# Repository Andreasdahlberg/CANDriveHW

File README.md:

# CANDriveHW
CANDrive is a brushed DC Motor Controller controlled via a CAN interface.

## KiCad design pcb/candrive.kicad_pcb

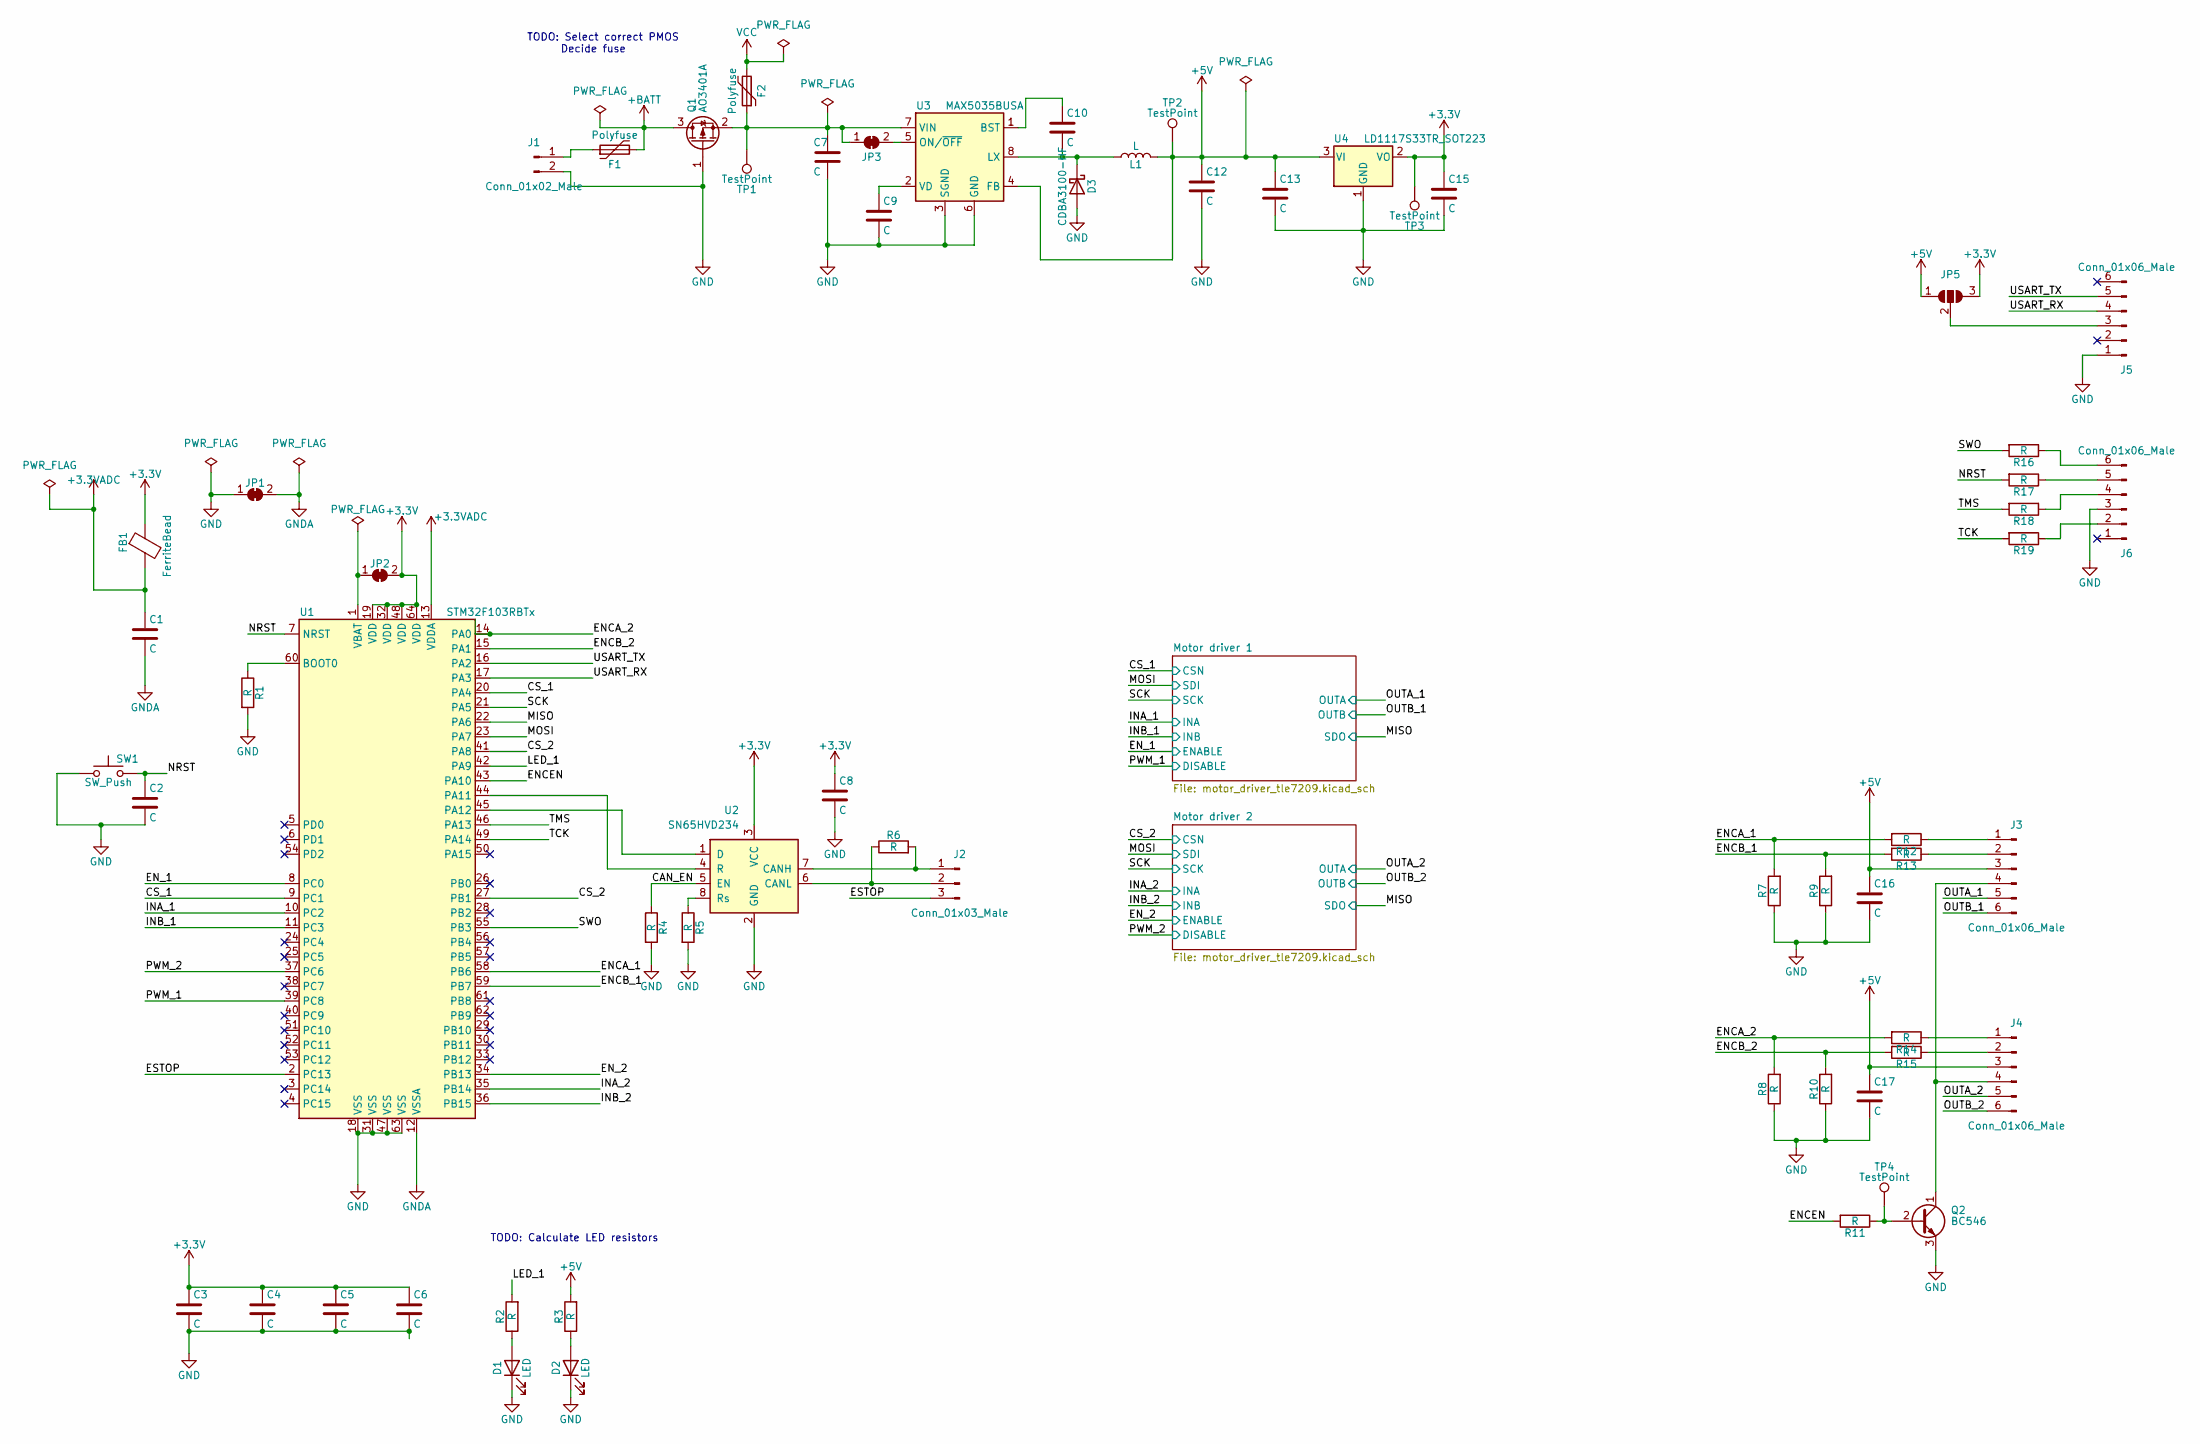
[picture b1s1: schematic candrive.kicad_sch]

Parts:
C1, C2, C3, C4, C5, C6, C7, C8, C9, C10, C12, C13, C15, C16, C17: C; C_0805_2012Metric_Pad1.18x1.45mm_HandSolder
D1, D2: LED; LED_0805_2012Metric_Pad1.15x1.40mm_HandSolder
D3: CDBA3100-HF; D_SMA
F1, F2: Polyfuse; Fuse_Bourns_MF-RHT300
FB1: FerriteBead; LairdTech_28C0236-0JW-10
J1: Conn_01x02_Male; PinHeader_1x02_P2.54mm_Horizontal
J2: Conn_01x03_Male; PinHeader_1x03_P2.54mm_Horizontal
J3, J4: Conn_01x06_Male; PinHeader_1x06_P2.54mm_Horizontal
J5, J6: Conn_01x06_Male; PinHeader_1x06_P2.54mm_Vertical
JP1, JP2, JP3: SolderJumper_2_Bridged; SolderJumper-2_P1.3mm_Open_TrianglePad1.0x1.5mm
JP5: SolderJumper_3_Open; SolderJumper-3_P2.0mm_Open_TrianglePad1.0x1.5mm
L1: L; L_0805_2012Metric_Pad1.05x1.20mm_HandSolder
Q1: AO3401A; SOT-23
Q2: BC546; TO-92_Inline
R1, R2, R3, R4, R5, R6, R7, R8, R9, R10, R11, R12, R13, R14, R15, R16, R17, R18, R19: R; R_0805_2012Metric_Pad1.20x1.40mm_HandSolder
SW1: SW_Push; SW_Push_1P1T_NO_CK_KSC6xxJ
TP1, TP2, TP3, TP4: TestPoint; TestPoint_THTPad_D1.0mm_Drill0.5mm
U1: STM32F103RBTx; LQFP-64_10x10mm_P0.5mm
U2: SN65HVD234; SOIC-8_3.9x4.9mm_P1.27mm
U3: MAX5035BUSA; SOIC-8_3.9x4.9mm_P1.27mm
U4: LD1117S33TR_SOT223; SOT-223-3_TabPin2

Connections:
+3.3V: C3.1, C4.1, C5.1, C6.1, C8.1, C15.1, FB1.1, JP2.2 (B), JP5.3 (B), TP3.1, U1.19 (VDD), U1.32 (VDD), U1.48 (VDD), U1.64 (VDD), U2.3 (VCC), U4.2 (VO)
+3.3VADC: C1.1, FB1.2, U1.13 (VDDA)
+5V: C12.1, C13.1, C16.1, C17.1, J3.3, J4.3, JP5.1 (A), L1.2, R3.2, TP2.1, U3.4 (FB), U4.3 (VI)
+BATT: F1.2, Q1.3 (D)
/CAN_EN: R4.1, U2.5 (EN)
/CS_1: U1.9 (PC1), U1.20 (PA4); also elsewhere on the board
/CS_2: U1.27 (PB1), U1.41 (PA8); also elsewhere on the board
/ENCA_1: R7.2, R12.2, U1.58 (PB6)
/ENCA_2: R8.2, R14.2, U1.14 (PA0)
/ENCB_1: R9.2, R13.2, U1.59 (PB7)
/ENCB_2: R10.2, R15.2, U1.15 (PA1)
/ENCEN: R11.2, U1.43 (PA10)
/EN_1: U1.8 (PC0); also elsewhere on the board
/EN_2: U1.34 (PB13); also elsewhere on the board
/ESTOP: J2.3, U1.2 (PC13)
/INA_1: U1.10 (PC2); also elsewhere on the board
/INA_2: U1.35 (PB14); also elsewhere on the board
/INB_1: U1.11 (PC3); also elsewhere on the board
/INB_2: U1.36 (PB15); also elsewhere on the board
/LED_1: R2.2, U1.42 (PA9)
/MISO: U1.22 (PA6); also elsewhere on the board
/MOSI: U1.23 (PA7); also elsewhere on the board
/NRST: C2.1, R17.2, SW1.2, U1.7 (NRST)
/OUTA_1: J3.5; also elsewhere on the board
/OUTA_2: J4.5; also elsewhere on the board
/OUTB_1: J3.6; also elsewhere on the board
/OUTB_2: J4.6; also elsewhere on the board
/PWM_1: U1.39 (PC8); also elsewhere on the board
/PWM_2: U1.37 (PC6); also elsewhere on the board
/SCK: U1.21 (PA5); also elsewhere on the board
/SWO: R16.2, U1.55 (PB3)
/TCK: R19.2, U1.49 (PA14)
/TMS: R18.2, U1.46 (PA13)
/USART_RX: J5.4, U1.17 (PA3)
/USART_TX: J5.5, U1.16 (PA2)
GND: C2.2, C3.2, C4.2, C5.2, C6.2, C7.2, C8.2, C9.2, C12.2, C13.2, C15.2, C16.2, C17.2, D1.1 (K), D2.1 (K), D3.2 (A), J1.2, J5.1, J6.3, JP1.1 (A), Q1.1 (G), Q2.3 (E), R1.2, R4.2, R5.2, R7.1, R8.1, R9.1, R10.1, SW1.1, U1.18 (VSS), U1.31 (VSS), U1.47 (VSS), U1.63 (VSS), U2.2 (GND), U3.3 (SGND), U3.6 (GND), U4.1 (GND); also elsewhere on the board
GNDA: C1.2, JP1.2 (B), U1.12 (VSSA)
unnamed: C7.1, F2.1, JP3.1 (A), Q1.2 (S), TP1.1, U3.7 (VIN)
unnamed: C9.1, U3.2 (VD)
unnamed: C10.1, U3.1 (BST)
unnamed: C10.2, D3.1 (K), L1.1, U3.8 (LX)
unnamed: D1.2 (A), R2.1
unnamed: D2.2 (A), R3.1
unnamed: F1.1, J1.1
unnamed: J2.1, R6.2, U2.7 (CANH)
unnamed: J2.2, R6.1, U2.6 (CANL)
unnamed: J3.1, R12.1
unnamed: J3.2, R13.1
unnamed: J3.4, J4.4, Q2.1 (C)
unnamed: J4.1, R14.1
unnamed: J4.2, R15.1
unnamed: J5.3, JP5.2 (C)
unnamed: J6.2, R19.1
unnamed: J6.4, R18.1
unnamed: J6.5, R17.1
unnamed: J6.6, R16.1
unnamed: JP2.1 (A), U1.1 (VBAT)
unnamed: JP3.2 (B), U3.5 (ON/~OFF)
unnamed: Q2.2 (B), R11.1, TP4.1
unnamed: R1.1, U1.60 (BOOT0)
unnamed: R5.1, U2.8 (Rs)
unnamed: U1.44 (PA11), U2.4 (R)
unnamed: U1.45 (PA12), U2.1 (D)
VCC: F2.2; also elsewhere on the board

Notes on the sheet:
TODO: Calculate LED resistors
TODO: Select correct PMOS Decide fuse

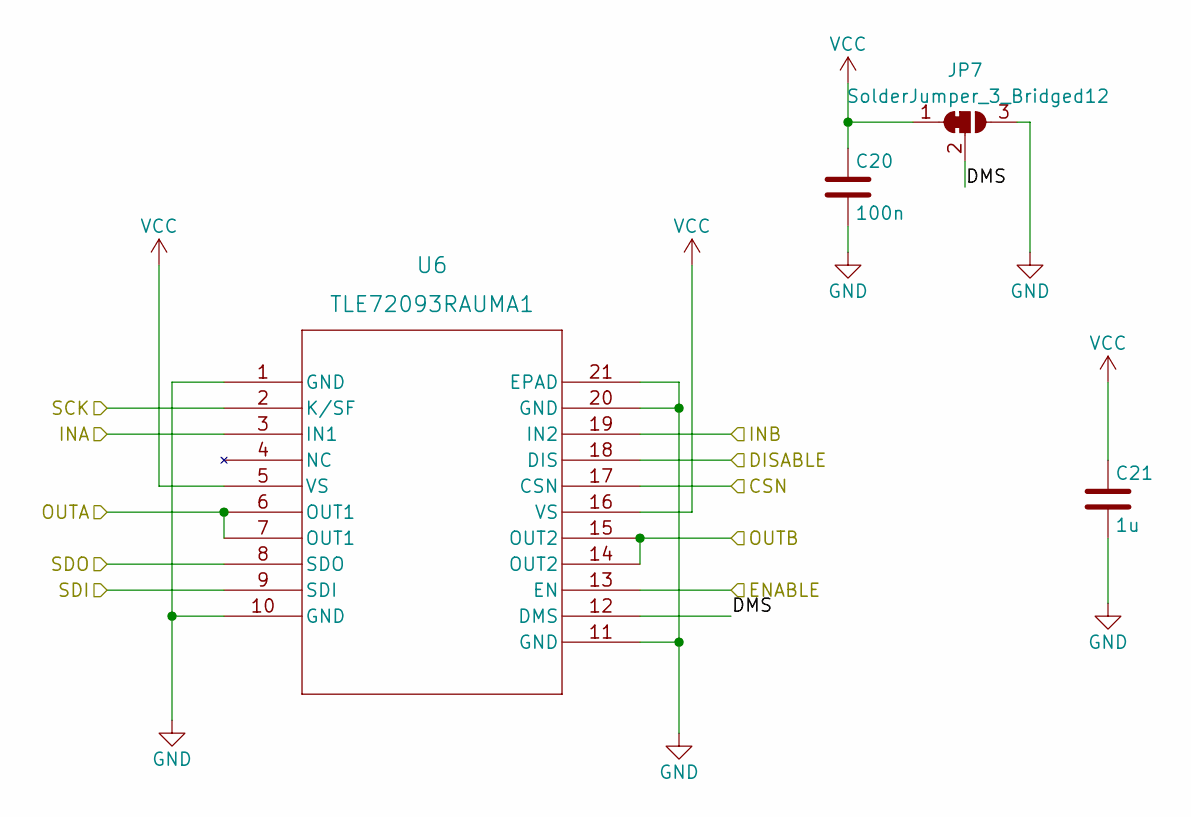
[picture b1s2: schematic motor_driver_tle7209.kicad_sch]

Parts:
C20: 100n; C_0805_2012Metric_Pad1.18x1.45mm_HandSolder
C21: 1u; C_0805_2012Metric_Pad1.18x1.45mm_HandSolder
JP7: SolderJumper_3_Bridged12; SolderJumper-3_P2.0mm_Open_TrianglePad1.0x1.5mm
U6: TLE72093RAUMA1; PG-DSO-20-65_11X15P9_INF

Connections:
/CS_1: U6.17 (CSN); also elsewhere on the board
/EN_1: U6.13 (EN); also elsewhere on the board
/INA_1: U6.3 (IN1); also elsewhere on the board
/INB_1: U6.19 (IN2); also elsewhere on the board
/MISO: U6.8 (SDO); also elsewhere on the board
/MOSI: U6.9 (SDI); also elsewhere on the board
/Motor driver 1/DMS: JP7.2 (C), U6.12 (DMS)
/OUTA_1: U6.6 (OUT1), U6.7 (OUT1); also elsewhere on the board
/OUTB_1: U6.14 (OUT2), U6.15 (OUT2); also elsewhere on the board
/PWM_1: U6.18 (DIS); also elsewhere on the board
/SCK: U6.2 (K/SF); also elsewhere on the board
GND: C20.2, C21.2, JP7.3 (B), U6.1 (GND), U6.10 (GND), U6.11 (GND), U6.20 (GND), U6.21 (EPAD); also elsewhere on the board
VCC: C20.1, C21.1, JP7.1 (A), U6.5 (VS), U6.16 (VS); also elsewhere on the board

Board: 4 copper layers, 70 parts (0 on the bottom side), 66 nets, no tracks yet.

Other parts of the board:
C18: 100n; C_0805_2012Metric_Pad1.18x1.45mm_HandSolder
C19: 1u; C_0805_2012Metric_Pad1.18x1.45mm_HandSolder
JP6: SolderJumper_3_Bridged12; SolderJumper-3_P2.0mm_Open_TrianglePad1.0x1.5mm
U5: TLE72093RAUMA1; PG-DSO-20-65_11X15P9_INF

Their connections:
/CS_2: U5.17 (CSN); also elsewhere on the board
/EN_2: U5.13 (EN); also elsewhere on the board
/INA_2: U5.3 (IN1); also elsewhere on the board
/INB_2: U5.19 (IN2); also elsewhere on the board
/MISO: U5.8 (SDO); also elsewhere on the board
/MOSI: U5.9 (SDI); also elsewhere on the board
/Motor driver 2/DMS: JP6.2 (C), U5.12 (DMS)
/OUTA_2: U5.6 (OUT1), U5.7 (OUT1); also elsewhere on the board
/OUTB_2: U5.14 (OUT2), U5.15 (OUT2); also elsewhere on the board
/PWM_2: U5.18 (DIS); also elsewhere on the board
/SCK: U5.2 (K/SF); also elsewhere on the board
GND: C18.2, C19.2, JP6.3 (B), U5.1 (GND), U5.10 (GND), U5.11 (GND), U5.20 (GND), U5.21 (EPAD); also elsewhere on the board
VCC: C18.1, C19.1, JP6.1 (A), U5.5 (VS), U5.16 (VS); also elsewhere on the board

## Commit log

2023-06-30 Initial commit of pcb files
2023-06-30 Add basic kibot config
2023-06-30 Add kibot workflow
2023-07-01 Restructure kibot config and workflows
2023-07-01 Ignore log files in workflow
2023-07-01 Fix incorrect artifact name
2023-07-02 Fix some ERC warnings
2023-07-04 Replace VNH7070BAS with TLE7209 in schematic
2023-07-04 Fix missing footprint error
2023-07-04 Fix broken footprint
    Parts of the center pad was not properly connected.
2023-07-04 Update PCB with new components
2023-07-08 Add missing footprint
2023-07-08 Update gitignore
